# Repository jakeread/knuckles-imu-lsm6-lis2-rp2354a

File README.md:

# Knuckles Accelerometer Module

> An IMU using the LSM6DSV16X accelerometer, LIS2MDL magnetometer, and RP2354A microcontroller. 

| | |
| --- | --- |
|  |  |
|  |  |
|  |  |

## Functional Description

This is an IMU module that pairs the LSM6DSV16X accelerometer with an LIS2MDL magnetometer, using an RP2354A microcontroller. It is part of a larger family of modular circuits that I call `knuckles` and are used to build machine controllers. The `knuckles` system is not yet public. This IMU will be used to improve kinematic and frequency response models with higher frequency data than I can currently capture. 

The RP2354A is connected to the LSM6 and LIS2 via two indepentent SPI busses, and the LSM6's two interrupt lines are also routed back to the RP2354A. The board also includes an RGB LED (using GPIOs) for RTOS status indication, and a WS2812-based RGB LED for application status. 

The board is programmed with a standard 10-pin SWD connector. Communication is done through a `backpack` connection, which interfaces to modular PHY circuits; this is part of the `knuckles` system: the interface can be extended for UART, USB, CAN, Ethernet, or Wireless links. 

I have also included a generic GPIO output on a JST-SH connector for adhoc applications (it may be useful and there was space). 

## Enclosure

The board can be mounted directly into a machine and enclosed there, or mounted into this enclosure and attached externally anywhere. This is intended to be printed in PETG and uses M2.5 hardware. 

## TODO

- bring up and test firmware

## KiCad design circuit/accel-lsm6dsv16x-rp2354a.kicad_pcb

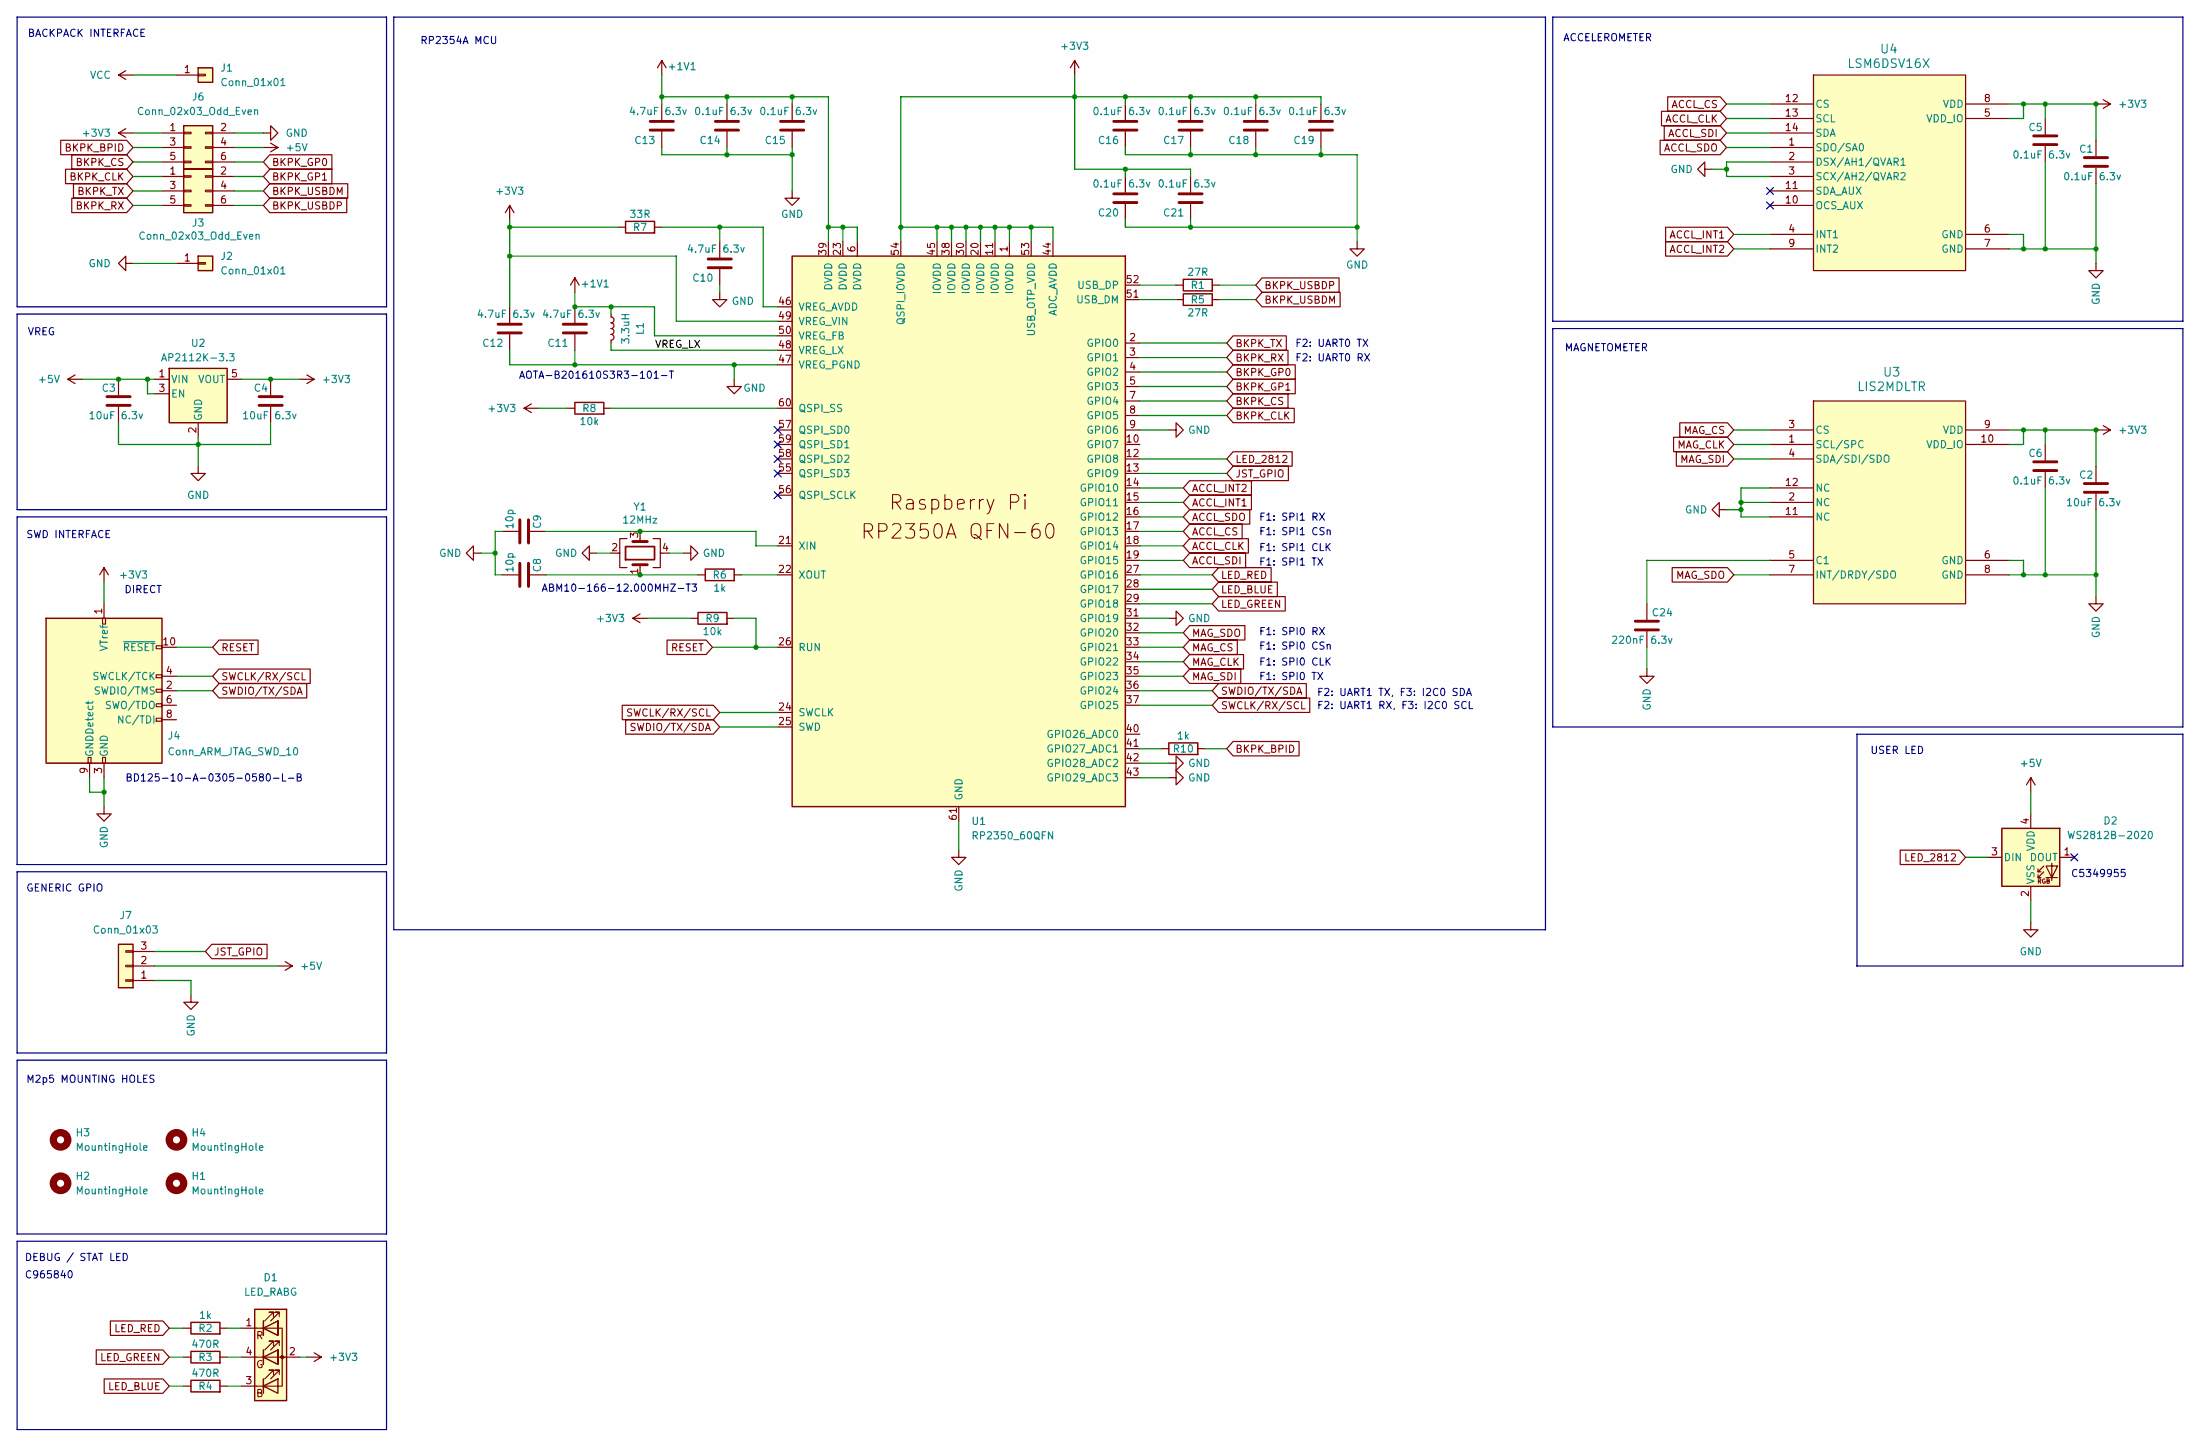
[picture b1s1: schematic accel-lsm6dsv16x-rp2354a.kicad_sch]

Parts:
C1, C5, C6, C14, C15, C16, C17, C18, C19, C20, C21: 0.1uF 6.3v; C_0402_1005Metric; MPN CC0402KRX7R5BB104
C2, C3, C4: 10uF 6.3v; C_0402_1005Metric; MPN MSASJ105CB5106MFNQ1D
C8, C9: 10p; C_0402_1005Metric; MPN CC0402JRNPO9BN100
C10, C11, C12, C13: 4.7uF 6.3v; C_0402_1005Metric; MPN CC0402MRX5R5BB475
C24: 220nF 6.3v; C_0402_1005Metric; MPN CC0402MRX5R5BB224
D1: LED_RABG; LED_RGB_1615; MPN XL-1615RGBC-RF; LCSC Part # C965840
D2: WS2812B-2020; LED_WS2812B-2020_PLCC4_2.0x2.0mm; MPN XL-2020RGBC-2812B; LCSC Part # C5349955
H1, H2, H3, H4: MountingHole; MountingHole_M2.5_Corner
J1, J2: Conn_01x01; Wurth_WA-SMST_M2_Thread_1.5mm_9774015243R; MPN SMTWEM215STR; DigiKey Part # 732-7069-6-ND
J3: Conn_02x03_Odd_Even; SpringTarget_2x03_Molex_0788641001; LCSC Part # DNP
J4: Conn_ARM_JTAG_SWD_10; PinHeader_2x05_P1.27mm_Vertical_SMD_Shrouded_BD125-10-A-030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; MPN FTSH-105-01-F-DV-K; LCSC Part # C5382952
J6: Conn_02x03_Odd_Even; SpringTarget_2x03_Molex_0788641001; Digikey Part # DNP
J7: Conn_01x03; JST_SH_SM03B-SRSS-TB_1x03-1MP_P1.00mm_Horizontal; MPN SM03B-SRSS-TB(LF)(SN); Digikey Part # 455-SM03B-SRSS-TBCT-ND
L1: 3.3uH; L_pol_2016; MPN AOTA-B201610S3R3-101-T; Digikey Part # AOTA-B201610S3R3-101-T
R1, R5: 27R; R_0402_1005Metric; MPN RC0402FR-0727RL
R2, R6, R10: 1k; R_0402_1005Metric; MPN RC0402FR-071KL
R3, R4: 470R; R_0402_1005Metric; MPN RC0402FR-07470RL
R7: 33R; R_0402_1005Metric; MPN RC0402FR-0733RL
R8, R9: 10k; R_0402_1005Metric; MPN RC0402FR-0710KL
U1: RP2350_60QFN; RP2350-QFN-60-1EP_7x7_P0.4mm_EP3.4x3.4mm; MPN RP2354A; LCSC Part # C41378174
U2: AP2112K-3.3; SOT-23-5; MPN AP2112K-3.3TRG1; LCSC Part # C51118
U3: LIS2MDLTR; LGA-12_2X2X1_STM; MPN LIS2MDLTR; Digikey Part # LIS2MDLTR
U4: LSM6DSV16X; LGA14_LSM6_STM; MPN LSM6DSV16XTR; Digikey Part # LSM6DSV16XTR
Y1: 12MHz; Crystal_SMD_2520-4Pin_2.5x2.0mm; MPN ABM10-166-12.000MHZ-T3; Digikey Part # 535-13520-1-ND

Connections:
+1V1: C11.2, C13.2, C14.2, C15.2, L1.1, U1.6 (DVDD), U1.23 (DVDD), U1.39 (DVDD), U1.50 (VREG_FB)
+3V3: C1.1, C2.1, C4.1, C5.1, C6.1, C12.2, C16.2, C17.2, C18.2, C19.2, C20.2, C21.2, D1.2 (A), J4.1 (VTref), J6.1, R7.1, R8.1, R9.1, U1.1 (IOVDD), U1.11 (IOVDD), U1.20 (IOVDD), U1.30 (IOVDD), U1.38 (IOVDD), U1.44 (ADC_AVDD), U1.45 (IOVDD), U1.49 (VREG_VIN), U1.53 (USB_OTP_VDD), U1.54 (QSPI_IOVDD), U2.5 (VOUT), U3.9 (VDD), U3.10 (VDD_IO), U4.5 (VDD_IO), U4.8 (VDD)
+5V: C3.1, D2.4 (VDD), J6.4, J7.2, U2.1 (VIN), U2.3 (EN)
/VREG_LX: L1.2, U1.48 (VREG_LX)
ACCL_CLK: U1.18 (GPIO14), U4.13 (SCL)
ACCL_CS: U1.17 (GPIO13), U4.12 (CS)
ACCL_INT1: U1.15 (GPIO11), U4.4 (INT1)
ACCL_INT2: U1.14 (GPIO10), U4.9 (INT2)
ACCL_SDI: U1.19 (GPIO15), U4.14 (SDA)
ACCL_SDO: U1.16 (GPIO12), U4.1 (SDO/SA0)
BKPK_BPID: J6.3, R10.2
BKPK_CLK: J3.1, U1.8 (GPIO5)
BKPK_CS: J6.5, U1.7 (GPIO4)
BKPK_GP0: J6.6, U1.4 (GPIO2)
BKPK_GP1: J3.2, U1.5 (GPIO3)
BKPK_RX: J3.5, U1.3 (GPIO1)
BKPK_TX: J3.3, U1.2 (GPIO0)
BKPK_USBDM: J3.4, R5.2
BKPK_USBDP: J3.6, R1.2
GND: C1.2, C2.2, C3.2, C4.2, C5.2, C6.2, C8.2, C9.2, C10.1, C11.1, C12.1, C13.1, C14.1, C15.1, C16.1, C17.1, C18.1, C19.1, C20.1, C21.1, C24.2, D2.2 (VSS), J2.1, J4.3 (GND), J4.5 (GND), J4.9 (GNDDetect), J6.2, J7.1, U1.9 (GPIO6), U1.31 (GPIO19), U1.42 (GPIO28_ADC2), U1.43 (GPIO29_ADC3), U1.47 (VREG_PGND), U1.61 (GND), U2.2 (GND), U3.2 (NC), U3.6 (GND), U3.8 (GND), U3.11 (NC), U3.12 (NC), U4.2 (DSX/AH1/QVAR1), U4.3 (SCX/AH2/QVAR2), U4.6 (GND), U4.7 (GND), Y1.2, Y1.4
JST_GPIO: J7.3, U1.13 (GPIO9)
LED_2812: D2.3 (DIN), U1.12 (GPIO8)
LED_BLUE: R4.1, U1.28 (GPIO17)
LED_GREEN: R3.1, U1.29 (GPIO18)
LED_RED: R2.1, U1.27 (GPIO16)
MAG_CLK: U1.34 (GPIO22), U3.1 (SCL/SPC)
MAG_CS: U1.33 (GPIO21), U3.3 (CS)
MAG_SDI: U1.35 (GPIO23), U3.4 (SDA/SDI/SDO)
MAG_SDO: U1.32 (GPIO20), U3.7 (INT/DRDY/SDO)
unnamed: C8.1, R6.1, Y1.1
unnamed: D1.3 (BK), R4.2
unnamed: D1.4 (GK), R3.2
unnamed: D1.1 (RK), R2.2
unnamed: R10.1, U1.41 (GPIO27_ADC1)
unnamed: R8.2, U1.60 (QSPI_SS)
unnamed: R5.1, U1.51 (USB_DM)
unnamed: R1.1, U1.52 (USB_DP)
unnamed: C10.2, R7.2, U1.46 (VREG_AVDD)
unnamed: C9.1, U1.21 (XIN), Y1.3
unnamed: R6.2, U1.22 (XOUT)
unnamed: C24.1, U3.5 (C1)
RESET: J4.10 (~RESET), R9.2, U1.26 (RUN)
SWCLK/RX/SCL: J4.4 (SWCLK/TCK), U1.24 (SWCLK), U1.37 (GPIO25)
SWDIO/TX/SDA: J4.2 (SWDIO/TMS), U1.25 (SWD), U1.36 (GPIO24)
VCC: J1.1

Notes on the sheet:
C965840
F1: SPI0 CSn
RP2354A MCU
C5349955
M2p5 MOUNTING HOLES
F2: UART1 RX, F3: I2C0 SCL
F1: SPI1 CSn
BD125-10-A-0305-0580-L-B
GENERIC GPIO
USER LED
MAGNETOMETER
F1: SPI1 TX
DIRECT
F1: SPI0 RX
VREG
F1: SPI0 CLK
DEBUG / STAT LED
F1: SPI1 RX
F2: UART0 RX
SWD INTERFACE
F2: UART0 TX
F1: SPI0 TX
BACKPACK INTERFACE
F1: SPI1 CLK
ABM10-166-12.000MHZ-T3
AOTA-B201610S3R3-101-T
F2: UART1 TX, F3: I2C0 SDA
ACCELEROMETER

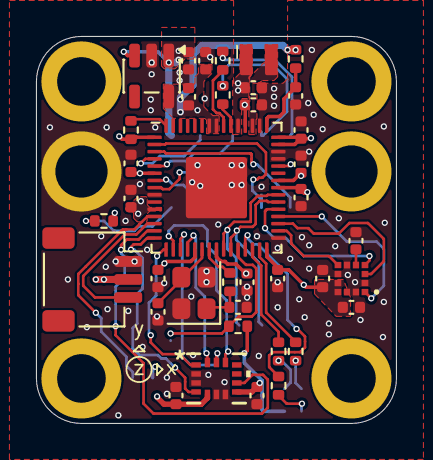
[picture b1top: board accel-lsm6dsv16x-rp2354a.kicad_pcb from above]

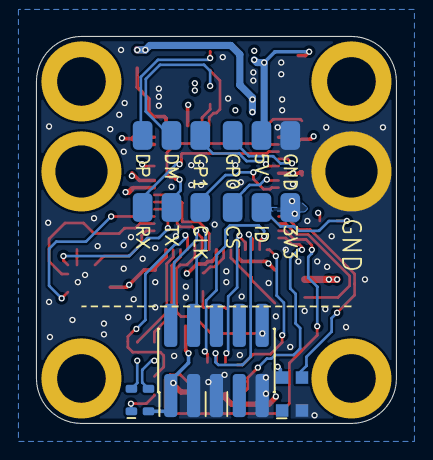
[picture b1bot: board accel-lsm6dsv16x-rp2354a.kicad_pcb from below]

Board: 4 copper layers, 20.0 x 21.5 mm, 49 parts (5 on the bottom side), 44 nets.

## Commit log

2026-01-12 add design files, etc
2026-01-12 schema img
2026-01-12 typo schema
2026-01-12 licenses (heavy handed) and firmware stub
2026-01-12 added functional description
2026-01-13 add circuit cad and enclosure
2026-01-28 upd8 some fw, images
